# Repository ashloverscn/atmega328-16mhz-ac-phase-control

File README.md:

# atmega328-16mhz-ac-phase-control
Control AC phase power using Arduino UNO and other atmega328 based Arduino Boards

dimmer pcb :

https://github.com/ashloverscn/dimmer-pcb

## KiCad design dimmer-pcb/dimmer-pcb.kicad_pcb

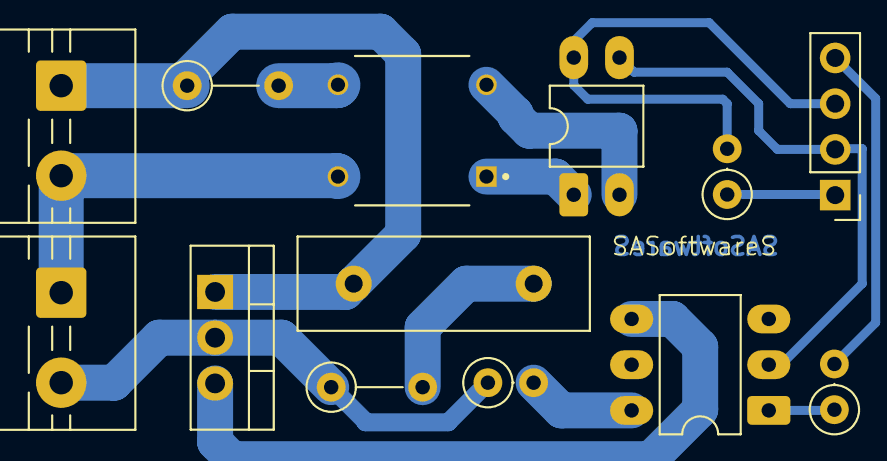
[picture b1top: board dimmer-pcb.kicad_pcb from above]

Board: 2 copper layers, 13 parts (0 on the bottom side), 14 nets.

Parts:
C1: 104J; C_Disc_D16.0mm_W5.0mm_P10.00mm
DB107: DB107; DIP825W50P509L880H320Q4
J1, J2: TerminalBlock_MaiXu_MX126-5.0-02P_1x02_P5.00mm
J3: Conn_01x04; PinHeader_1x04_P2.54mm_Vertical
Q1: BT136; TO-220-3_Vertical
R1: 100k; R_Axial_DIN0207_L6.3mm_D2.5mm_P5.08mm_Vertical
R2: 39; R_Axial_DIN0207_L6.3mm_D2.5mm_P5.08mm_Vertical
R3: 1k; R_Axial_DIN0207_L6.3mm_D2.5mm_P2.54mm_Vertical
R4: 10k; R_Axial_DIN0207_L6.3mm_D2.5mm_P2.54mm_Vertical
R5: 330; R_Axial_DIN0207_L6.3mm_D2.5mm_P2.54mm_Vertical
U1: PC817; DIP-4_W7.62mm_LongPads
U3: MOC3021; DIP-6_W7.62mm_LongPads

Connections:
+5V: J3.1, R4.1
GND: J3.2, U1.3, U3.2
unnamed: DB107.1, U1.1
unnamed: DB107.2, U1.2
unnamed: DB107.3, R1.2
unnamed: C1.1, R2.2
unnamed: C1.2, J1.1, Q1.1 (A1), R1.1
unnamed: DB107.4, J1.2, J2.1
unnamed: J2.2, Q1.2 (A2), R2.1, R3.1
unnamed: J3.3, R4.2, U1.4
unnamed: J3.4, R5.2
unnamed: Q1.3 (G), U3.4
unnamed: R3.2, U3.6
unnamed: R5.1, U3.1

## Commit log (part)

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2017-12-17 Add files via upload
    This Library controls 50Hz AC phase power using Arduino UNO and other atmega328 and atmega168 based Arduino Boards
